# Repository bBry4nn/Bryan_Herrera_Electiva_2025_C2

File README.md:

# Bryan_Herrera_Electiva_2025_C2

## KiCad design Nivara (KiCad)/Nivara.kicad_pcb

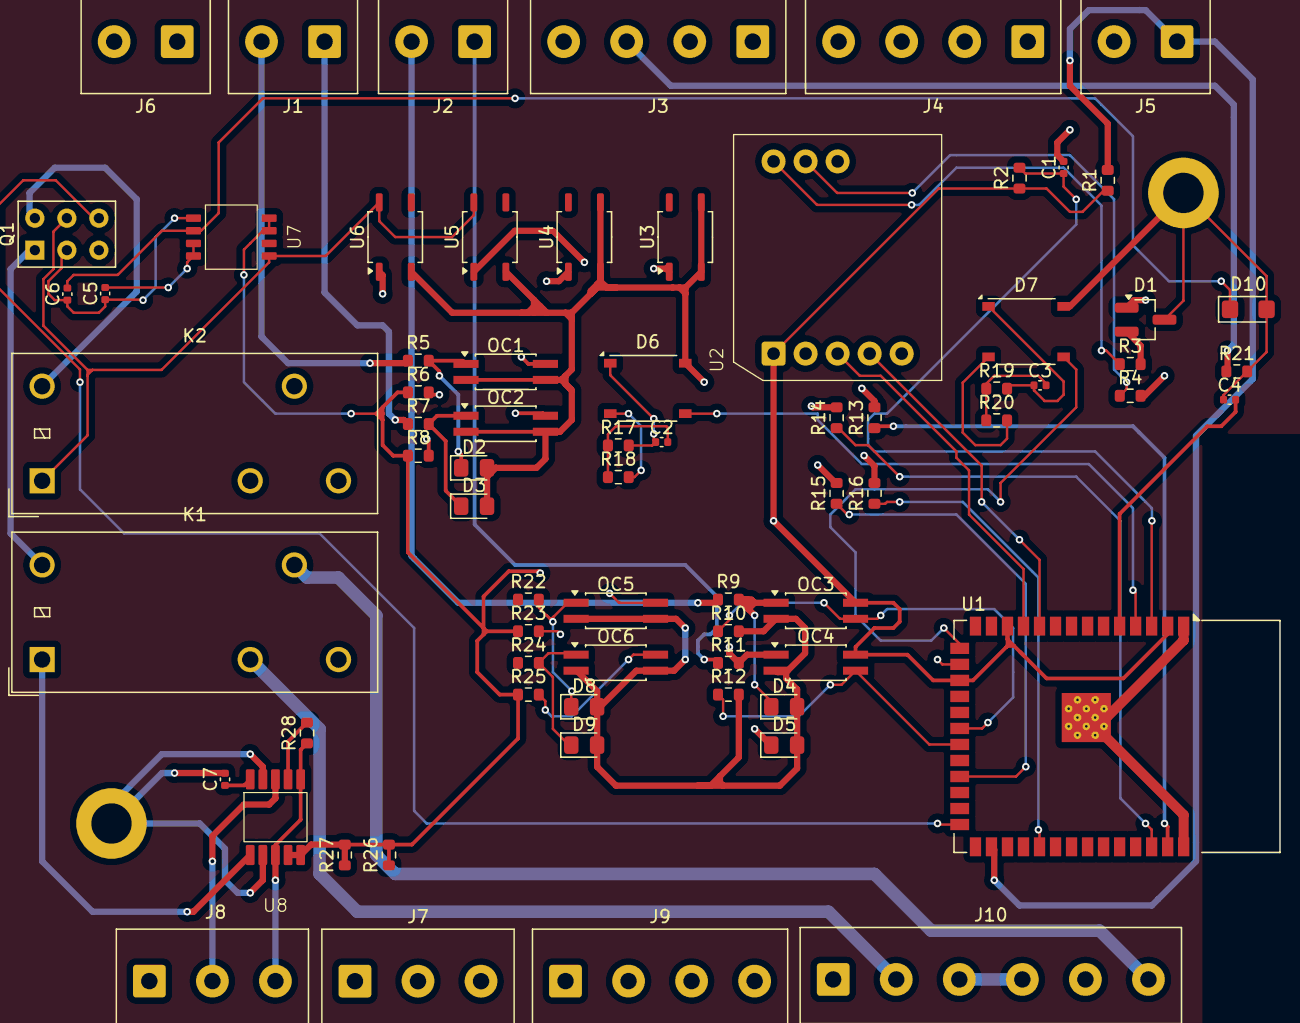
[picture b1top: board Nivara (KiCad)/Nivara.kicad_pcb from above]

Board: 4 copper layers, 72 parts (0 on the bottom side), 56 nets.

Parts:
C1, C2, C3, C4, C5, C6, C7: C_0603; C_0402_1005Metric
D1: SM712_SOT23; SOT-23_Handsoldering
D2, D3, D4, D5, D8, D9: DL4007; D_0805_2012Metric_Pad1.15x1.40mm_HandSolder
D6, D7: MB24F_C7427849; Diode_Bridge_Diotec_ABS
D10: SMF24A; D_SMF
J1, J2, J5, J6: Screw_Terminal_2_P5.00mm; TerminalBlock_Phoenix_PT-1,5-2-5.0-H_1x02_P5.00mm_Horizontal
J3, J4, J9: Screw_Terminal_4_P5.00mm; TerminalBlock_Phoenix_PT-1,5-4-5.0-H_1x04_P5.00mm_Horizontal
J7, J8: Screw_Terminal_3_P5.00mm; TerminalBlock_Phoenix_PT-1,5-3-5.0-H_1x03_P5.00mm_Horizontal
J10: Screw_Terminal_6_P5.00mm; TerminalBlock_Phoenix_PT-1,5-6-5.0-H_1x06_P5.00mm_Horizontal
K1, K2: G2RL-1; Relay_SPDT_Omron_G2RL-1
OC1, OC2, OC3, OC4, OC5, OC6: LTV-357T-B; SO-4_4.4x2.3mm_P1.27mm
Q1: SW_NKK_G1xJP
R1, R2, R3, R4, R5, R6, R7, R8, R9, R10, R11, R12, R13, R14, R15, R16, R17, R18, R19, R20, R21, R22, R23, R24, R25, R26, R27, R28: R_0603; R_0603_1608Metric
U1: ESP32-S3-WROOM-1
U2: RSM3485ECHT
U3, U4, U5, U6: GAQY211G2S; SOP-4_3.8x4.1mm_P2.54mm
U7: GP8201S-TC50-EW; GP8201S
U8: GP8303-TC50-EW; GP8303

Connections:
+3.3V: OC3.4, OC4.4, R1.1, R2.1, R6.1, R8.1, R23.1, R25.1, R26.1, R26.2, R27.1, R27.2, U1.2 (3V3), U1.12 (GPIO8/TOUCH8/ADC1_CH7/SUBSPICS1), U1.17 (GPIO9/TOUCH9/ADC1_CH8/FSPIHD/SUBSPIHD), U2.1 (VCC), U7.1 (SCLK), U7.2 (SDA), U8.1 (SLCK), U8.2 (SDA)
/Board/0_10mA/Ang_Out: C6.2, D10.1 (K), U7.6 (VOUT)
/Board/0v_10v/0v_10V: D6.3 (C1), U1.4 (GPIO4/TOUCH4/ADC1_CH3)
/Board/0v_32v/0V_32V: D7.3 (C1), U1.15 (GPIO3/TOUCH3/ADC1_CH2)
/Board/0v_32v/Analog_0-32_IN1: C3.2, R19.1, R20.1
/Board/Analog_0_10_IN1: C2.2, R17.1, R18.1
/Board/Analog_4-20_IN1: C4.2, J3.3, R21.1, U1.5 (GPIO5/TOUCH5/ADC1_CH4)
/Board/Analog_4_20_OUT1: J8.2, U8.8 (IOUT)
/Board/Digit_module/Plu_Digit_IN1: OC5.4, R23.2
/Board/Digit_module/Plu_Digit_IN2: OC6.4, R25.2
/Board/Input_NPN/NPN-Digit_IN1: OC1.4, R6.2
/Board/Input_NPN/NPN-Digit_IN2: OC2.4, R8.2
/Board/Input_PNP/PNP_Dig1: OC3.3, R10.1, U1.20 (GPIO12/TOUCH12/ADC2_CH1/FSPICLK/FSPIIO6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)
/Board/Input_PNP/PNP_Dig2: OC4.3, R12.1, U1.21 (GPIO13/TOUCH13/ADC2_CH2/FSPIQ/FSPIIO7/S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)
/Board/NPN_IN1: J1.2, R5.1
/Board/NPN_IN2: J1.1, R7.1
/Board/Output_NPN/NPN_IN0: R13.1, U1.39 (GPIO1/TOUCH1/ADC1_CH0)
/Board/Output_NPN/NPN_IN1: R14.1, U1.38 (GPIO2/TOUCH2/ADC1_CH1)
/Board/Output_PNP/PNP_input_0: R15.1, U1.23 (GPIO21)
/Board/Output_PNP/PNP_input_1: R16.1, U1.31 (GPIO38/FSPIWP/SUBSPIWP)
/Board/PNP_IN1: J2.2, R9.1
/Board/PNP_IN2: J2.1, R11.1
/Board/RLY1/RLY_Enable_1: Q1.3 (1B), U1.16 (GPIO46)
/Board/RLY1/RLY_Enable_2: Q1.4 (2B), U1.26 (GPIO45)
/Board/RLY_1_NO: J10.3, J10.4
/Board/RLY_2_COM: J10.6, K1.11
/Board/RLY_2_NC: J10.2, K1.12
/Board/RS485/UART_IN: U1.10 (GPIO17/U1TXD/ADC2_CH6), U2.4 (RXD)
/Board/RS485/UART_OUT: U1.11 (GPIO18/U1RXD/ADC2_CH7/CLK_OUT3), U2.3 (TXD)
/Board/RS485_A: D1.2 (A2), R3.2
/Board/RS485_B: D1.1 (A1), R4.2
/Board/Start | Stop: J5.1, R1.2, U1.28 (SPIIO6/GPIO35/FSPID/SUBSPID)
GND: C1.2, C4.1, C5.1, C6.1, C7.2, D1.3 (common), D2.2 (A), D3.2 (A), D4.2 (A), D5.2 (A), D6.4 (C2), D7.4 (C2), D8.2 (A), D9.2 (A), D10.2 (A), J3.4, J5.2, J6.1, J7.3, J8.3, OC1.2, OC1.3, OC2.2, OC2.3, OC3.2, OC4.2, OC5.2, OC5.3, OC6.2, OC6.3, Q1.2 (E), R10.2, R12.2, R21.2, R28.1, U1.1 (GND), U1.40 (GND), U1.41 (GND), U2.2 (GND), U3.2, U3.3, U4.2, U4.3, U5.2, U6.2, U7.5 (GND), U8.3 (A0), U8.4 (A1), U8.6 (GND), U8.9 (A2)
unnamed: D2.1 (K), OC1.1, R5.2
unnamed: D3.1 (K), OC2.1, R7.2
unnamed: D4.1 (K), OC3.1, R9.2
unnamed: D5.1 (K), OC4.1, R11.2
unnamed: D6.2 (+), R18.2
unnamed: C2.1, D6.1 (-), R17.2
unnamed: D7.2 (+), R20.2
unnamed: C3.1, D7.1 (-), R19.2
unnamed: D8.1 (K), OC5.1, R22.2
unnamed: D9.1 (K), OC6.1, R24.2
unnamed: K1.A2, Q1.1 (1C)
unnamed: K2.A2, Q1.6 (2C)
unnamed: R13.2, U3.1
unnamed: R14.2, U4.1
unnamed: R15.2, U5.1
unnamed: R16.2, U6.1
unnamed: C1.1, R2.2, U1.3 (EN)
unnamed: R4.1, U2.7 (A)
unnamed: R3.1, U2.6 (B)
unnamed: C5.2, U7.7 (SEL), U7.8 (V5V)
unnamed: R28.2, U8.7 (SET)
unnamed: C7.1, U8.10 (V5V)
VCC: J6.2, K1.A1, K2.A1, Q1.5 (COM), U5.4, U6.4, U7.4 (VCC), U8.5 (VCC)

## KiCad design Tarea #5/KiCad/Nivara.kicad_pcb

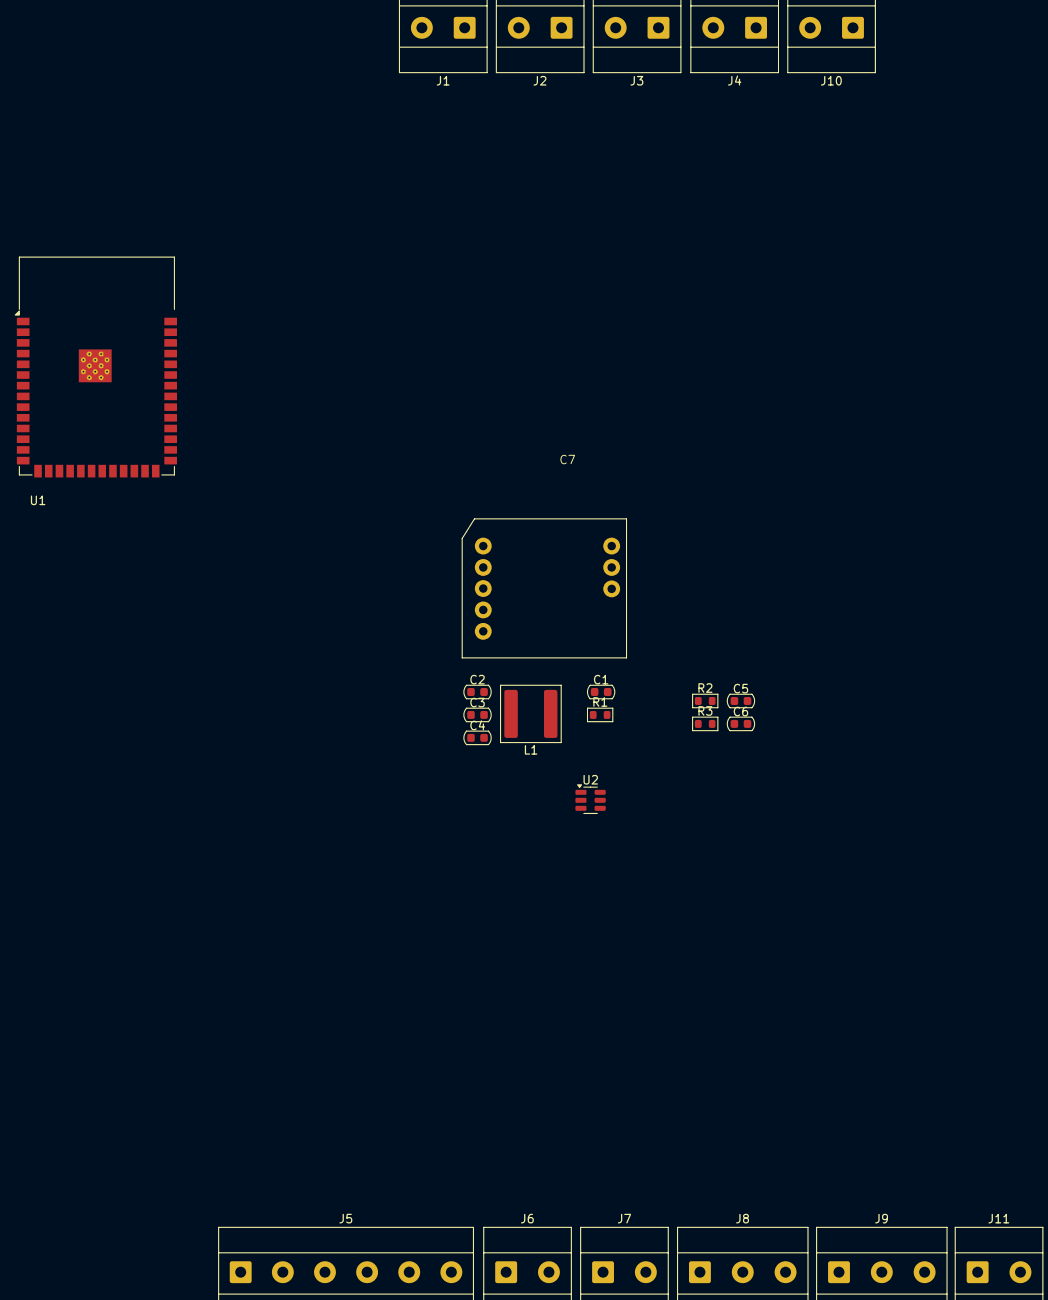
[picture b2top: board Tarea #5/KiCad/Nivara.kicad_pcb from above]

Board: 2 copper layers, 24 parts (0 on the bottom side), 7 nets, no tracks yet.

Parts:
C1: 1u; C_0603_1608Metric
C2: C_0603; C_0603_1608Metric
C3, C4: 100pF; C_0603_1608Metric
C5, C6: 22uF; C_0603_1608Metric
C7: C2992406
J1: IN NPN; TerminalBlock_Phoenix_MKDS-1,5-2-5.08_1x02_P5.08mm_Horizont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
J2: IN PNP; TerminalBlock_Phoenix_MKDS-1,5-2-5.08_1x02_P5.08mm_Horizont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
J3: IN 0-32V; TerminalBlock_Phoenix_MKDS-1,5-2-5.08_1x02_P5.08mm_Horizont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
J4: IN 0-10V; TerminalBlock_Phoenix_MKDS-1,5-2-5.08_1x02_P5.08mm_Horizont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
J5: Relay; TerminalBlock_Phoenix_MKDS-1,5-6_1x06_P5.00mm_Horizontal
J6: IN 4-20mA; TerminalBlock_Phoenix_MKDS-1,5-2-5.08_1x02_P5.08mm_Horizont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
J7: OUT 4-20mA; TerminalBlock_Phoenix_MKDS-1,5-2-5.08_1x02_P5.08mm_Horizont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
J8: OUT 0-10V; TerminalBlock_Phoenix_MKDS-1,5-3-5.08_1x03_P5.08mm_Horizont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
J9: Module RS485; TerminalBlock_Phoenix_MKDS-1,5-3-5.08_1x03_P5.08mm_Horizont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
J10: Terminal; TerminalBlock_Phoenix_MKDS-1,5-2-5.08_1x02_P5.08mm_Horizont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
J11: Screw_Terminal_01x02; TerminalBlock_Phoenix_MKDS-1,5-2-5.08_1x02_P5.08mm_Horizont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
L1: L_Iron; L_Bourns-SRN6028
R1: R_0603; R_0603_1608Metric
R2, R3: 22k; R_0603_1608Metric
U1: ESP32-S3-WROOM-1
U2: AP63203WU; TSOT-23-6

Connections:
+3.3V: C4.1, C5.1, C6.1, L1.2, R1.1, R2.1, U1.2 (3V3)
GND: C1.2, C5.2, C6.2, J3.2, J4.2, J6.2, J7.2, J8.3, J9.3, J11.2, R3.2, U1.1 (GND), U1.40 (GND), U1.41 (GND), U2.4 (GND)
unnamed: C1.1, R1.2, U1.3 (EN)
unnamed: C3.1, U2.6 (BST)
unnamed: C4.2, R2.2, R3.1, U2.1 (FB)
unnamed: C3.2, L1.1, U2.5 (SW)
VCC: C2.1, J11.1, U2.2 (EN), U2.3 (IN)

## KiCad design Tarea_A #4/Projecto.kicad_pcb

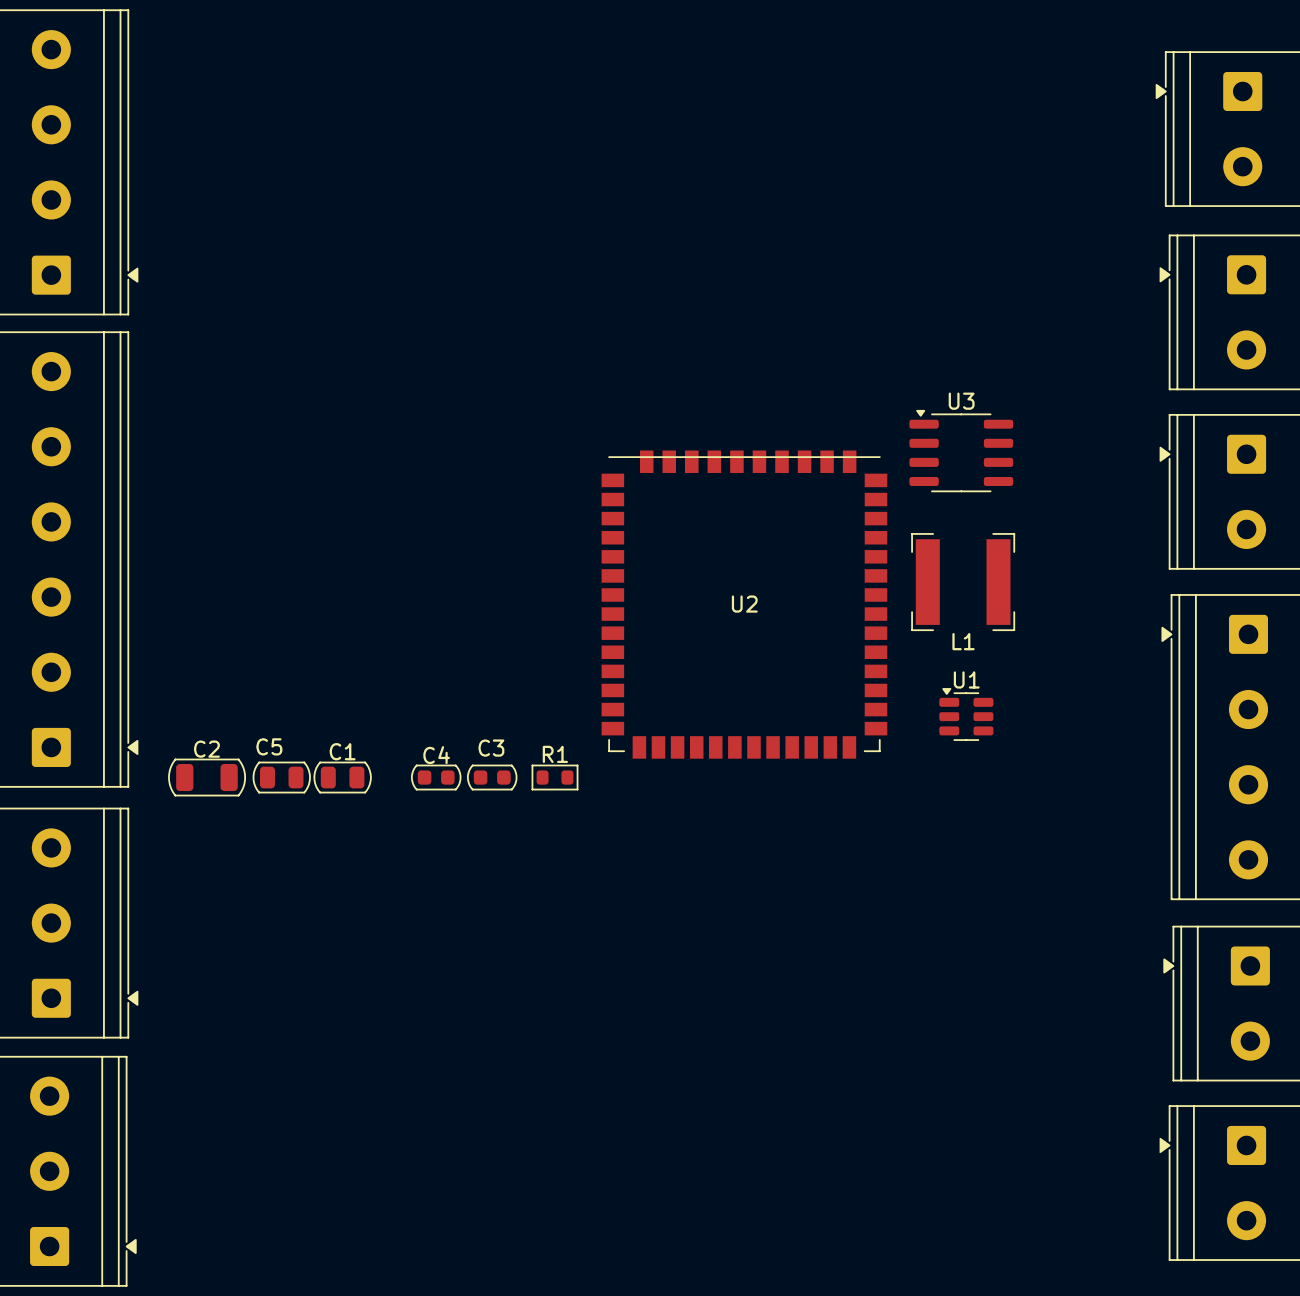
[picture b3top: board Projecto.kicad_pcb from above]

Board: 2 copper layers, 20 parts (0 on the bottom side), 11 nets, no tracks yet.

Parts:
C1, C5: C_0805; C_0805_2012Metric
C2: C_1206; C_1206_3216Metric
C3, C4: C_0603; C_0603_1608Metric
J1, J2, J3, J5, J6: Screw_Terminal_2_P5.00mm; TerminalBlock_Phoenix_PT-1,5-2-5.0-H_1x02_P5.00mm_Horizontal
J4, J9: Screw_Terminal_4_P5.00mm; TerminalBlock_Phoenix_PT-1,5-4-5.0-H_1x04_P5.00mm_Horizontal
J7, J8: Screw_Terminal_3_P5.00mm; TerminalBlock_Phoenix_PT-1,5-3-5.0-H_1x03_P5.00mm_Horizontal
J10: Screw_Terminal_6_P5.00mm; TerminalBlock_Phoenix_PT-1,5-6-5.0-H_1x06_P5.00mm_Horizontal
L1: L_Iron; L_Bourns-SRN6028
R1: R_0603; R_0603_1608Metric
U1: AP63203WU; TSOT-23-6
U2: ESP32-S3-WROOM-1
U3: MAX3485; SOIC-8_3.9x4.9mm_P1.27mm

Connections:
+3.3V: C1.1, C5.1, L1.2, R1.1, U1.1 (FB), U2.2 (3V3), U3.8 (VCC)
/Board_NIVARA/Driver_RS485/CONTROL_PIN: U3.2 (~RE), U3.3 (DE)
/Board_NIVARA/Driver_RS485/UART_IN: U2.37 (U0TXD/GPIO43/CLK_OUT1), U3.4 (DI)
/Board_NIVARA/Driver_RS485/UART_OUT: U2.36 (U0RXD/GPIO44/CLK_OUT2), U3.1 (RO)
/Board_NIVARA/RS485-A: J7.1, U3.6 (A)
/Board_NIVARA/RS485-B: J7.2, U3.7 (B)
GND: C1.2, C2.2, C4.2, C5.2, J1.1, J4.4, J6.2, J7.3, J8.3, U1.4 (GND), U2.1 (GND), U2.40 (GND), U3.5 (GND)
unnamed: C3.1, U1.6 (BST)
unnamed: C3.2, L1.1, U1.5 (SW)
unnamed: C4.1, R1.2, U2.3 (EN)
VCC: C2.1, J1.2, U1.2 (EN), U1.3 (IN)
